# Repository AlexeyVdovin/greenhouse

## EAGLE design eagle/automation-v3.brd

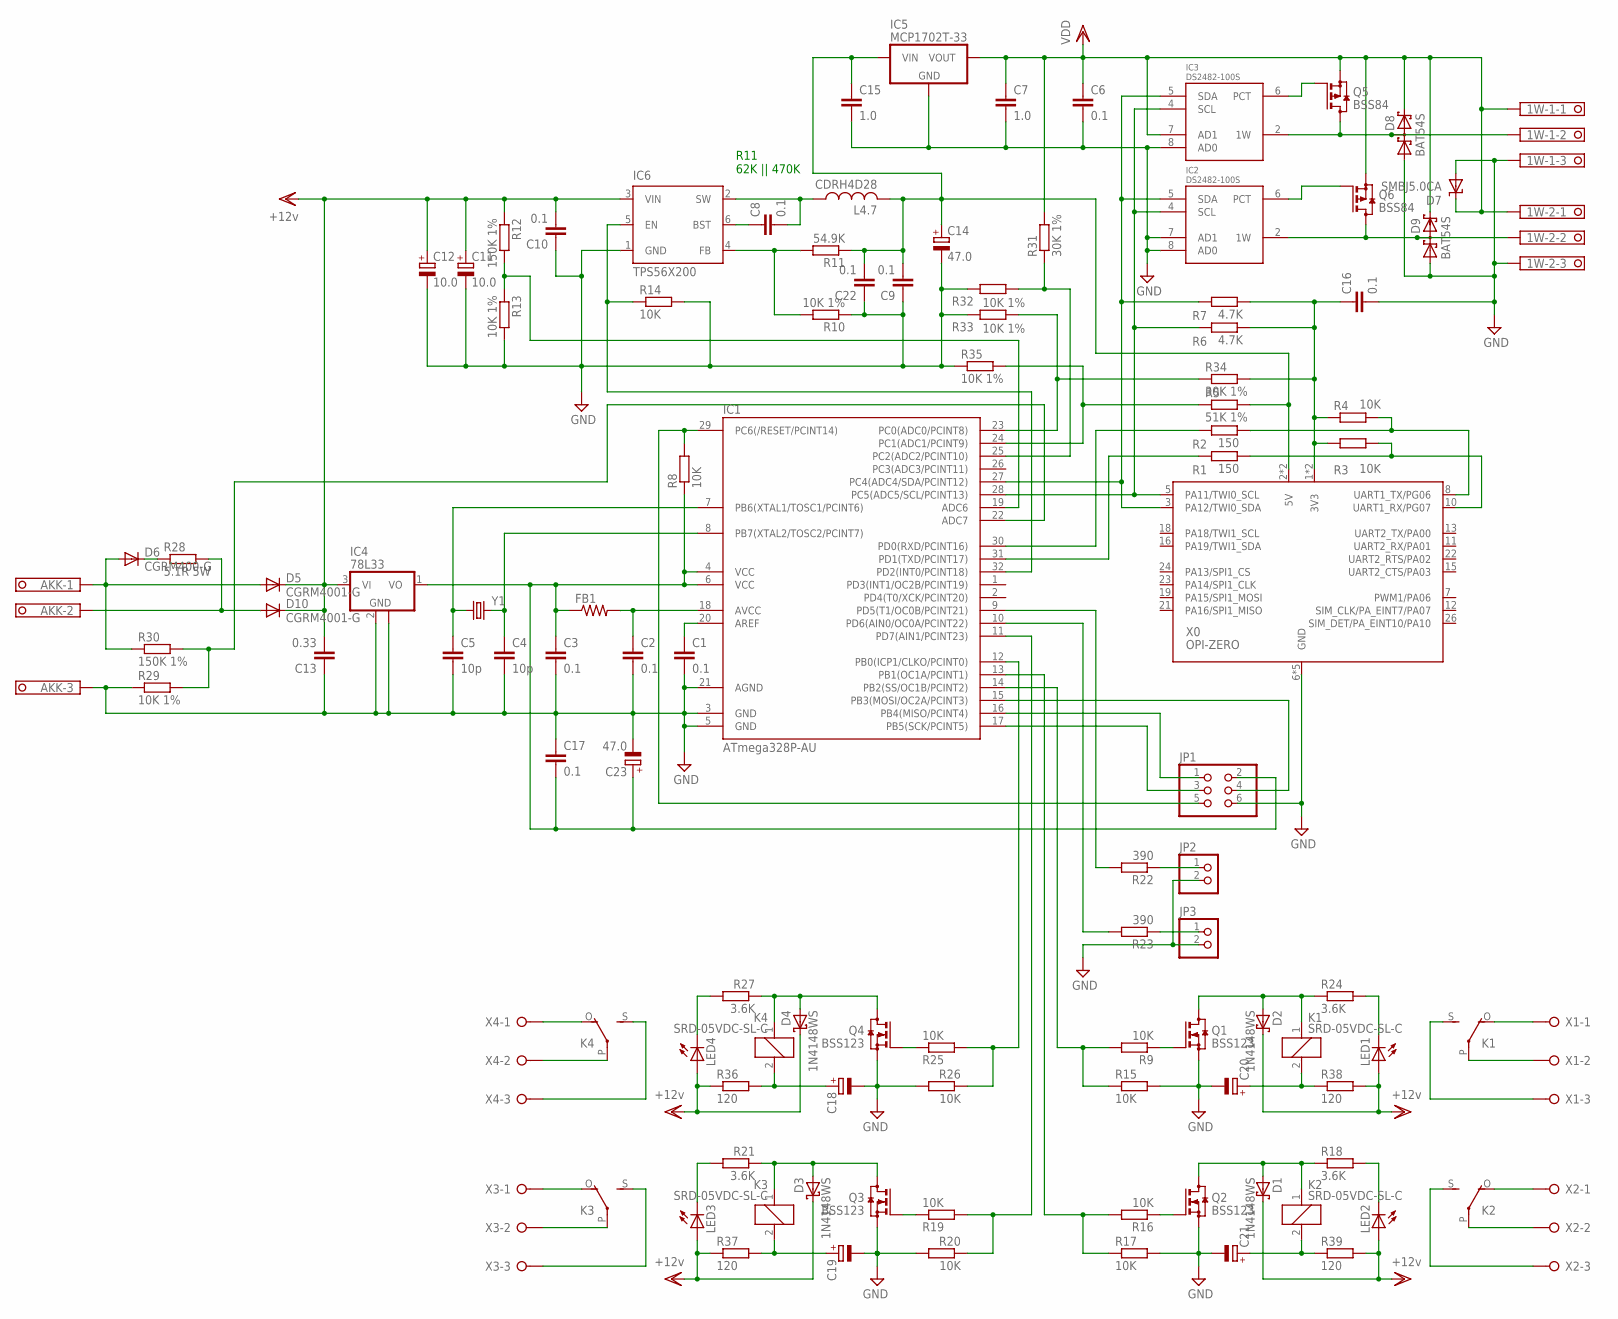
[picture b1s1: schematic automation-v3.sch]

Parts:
1W-1, 1W-2: 1751251
AKK: 1751251
C1, C2, C3, C6, C16, C17: 0.1; C0603
C4, C5: 10p; C0603
C7, C15: 1.0; C0805
C8, C9, C10, C22: 0.1; C0805
C11, C12: 10.0; C/6032-28R
C13: 0.33; C0805
C14, C23: 47.0; B/3528-21R
C18, C19, C20, C21: CPOL-EUE5-10.5; E5-10,5
D1, D2, D3, D4: 1N4148WS; SOD323_ST
D5, D10: CGRM4001-G; SOD-123_MINI-SMA
D6: CGRM400-G; SOD-123_MINI-SMA
D7: SMBJ5.0CA; SMBJ
D8, D9: BAT54S; SOT23
FB1: R-US_R0805; R0805
IC1: ATmega328P-AU; TQFP32-08
IC2, IC3: DS2482-100S; SO08
IC4: 78L33; SOT89
IC5: MCP1702T-33; SOT23-3-ROTATED
IC6: TPS56X200; TSOT23-6_DDC
JP1: PINHD-2X3; 2X03
JP2, JP3: PINHD-1X2; 1X02
K1, K2, K3, K4: SRD-05VDC-SL-C; NRP18
L4.7: CDRH4D28
LED1, LED2, LED3, LED4: LEDSML0805; SML0805
Q1, Q2, Q3, Q4: BSS123; SOT23
Q5, Q6: BSS84; SOT23
R1, R2: 150; R0603
R3, R4, R8, R9, R14, R15, R16, R17, R19, R20, R25, R26: 10K; R0603
R5: 51K 1%; R0603
R6, R7: 4.7K; R0603
R10, R13, R29, R32, R33, R35: 10K 1%; R0603
R11: 54.9K; R0603
R12, R30: 150K 1%; R0603
R18, R21, R24, R27: 3.6K; R0603
R22, R23: 390; R0603
R28: 5.1R 5W; VTA55
R31, R34: 30K 1%; R0603
R36, R37, R38, R39: 120; M1206
X0: OPI-ZERO; OPI0
X1, X2, X3, X4: W237-03P; W237-133
Y1: CRYSTALHC49US; HC49US

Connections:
12V: C10.2, C11.+, C12.+, C13.2, D1.C, D2.C, D3.C, D4.C, D5.C, D10.C, IC4.3 (VI), IC6.3 (VIN), LED1.A, LED2.A, LED3.A, LED4.A, R12.1, R36.1, R37.1, R38.2, R39.2
GND: 1W-1.3, 1W-2.3, AKK.3, C1.2, C2.2, C3.2, C4.2, C5.2, C6.2, C7.2, C9.1, C10.1, C11.-, C12.-, C13.1, C14.-, C15.2, C16.2, C17.1, C18.-, C19.-, C20.-, C21.-, C22.1, C23.-, D7.A, D8.1 (A1), D9.1 (A1), IC1.3 (GND), IC1.5 (GND), IC1.21 (AGND), IC2.3 (GND), IC2.7 (AD1), IC2.8 (AD0), IC3.3 (GND), IC3.8 (AD0), IC4.2 (GND), IC4.2@1 (GND), IC5.1 (GND), IC6.1 (GND), JP1.6, JP2.2, JP3.2, Q1.2 (S), Q2.2 (S), Q3.2 (S), Q4.2 (S), R10.1, R13.2, R14.2, R15.2, R17.2, R20.2, R26.2, R29.1, R32.2, R33.2, R35.1, X0.6 (GND), X0.9 (GND), X0.14 (GND), X0.20 (GND), X0.25 (GND)
unnamed: C8.2, IC6.2 (SW), L4.7.P$1 (1)
unnamed: C4.1, IC1.8 (PB7(XTAL2/TOSC2/PCINT7)), Y1.2
unnamed: IC1.30 (PD0(RXD/PCINT16)), R2.1
unnamed: IC1.31 (PD1(TXD/PCINT17)), R1.1
unnamed: R1.2, R3.2, X0.10 (UART1_RX/PG07)
unnamed: R2.2, R4.2, X0.8 (UART1_TX/PG06)
unnamed: C18.+, K4.2, R36.2
unnamed: C5.1, IC1.7 (PB6(XTAL1/TOSC1/PCINT6)), Y1.1
unnamed: IC1.24 (PC1(ADC1/PCINT9)), R5.1, R35.2
unnamed: AKK.1, D5.A, D6.A, R30.1
unnamed: IC1.29 (PC6(/RESET/PCINT14)), JP1.5, R8.2
unnamed: C19.+, K3.2, R37.2
unnamed: C1.1, IC1.20 (AREF)
unnamed: C2.1, FB1.2, IC1.18 (AVCC)
unnamed: C8.1, IC6.6 (BST)
unnamed: IC1.15 (PB3(MOSI/OC2A/PCINT3)), JP1.4
unnamed: IC1.17 (PB5(SCK/PCINT5)), JP1.3
unnamed: IC1.16 (PB4(MISO/PCINT4)), JP1.1
unnamed: IC3.6 (PCT), Q5.1 (G)
unnamed: IC6.4 (FB), R10.2, R11.2
unnamed: IC1.14 (PB2(SS/OC1B/PCINT2)), R9.2, R15.1
unnamed: IC1.13 (PB1(OC1A/PCINT1)), R16.2, R17.1
unnamed: IC1.19 (ADC6), R12.2, R13.1
unnamed: Q1.1 (G), R9.1
unnamed: IC1.32 (PD2(INT0/PCINT18)), IC6.5 (EN), R14.1
unnamed: K1.P, X1.2
unnamed: D6.C, R28.1
unnamed: 1W-1.2, D8.3 (C1A2), IC3.2 (1W), Q5.3 (D)
unnamed: AKK.2, D10.A, R28.2
unnamed: K1.S, X1.3
unnamed: K1.O, X1.1
unnamed: Q2.1 (G), R16.1
unnamed: D1.A, K2.1, Q2.3 (D), R18.1
unnamed: LED2.C, R18.2
unnamed: IC1.10 (PD6(AIN0/OC0A/PCINT22)), R23.2
unnamed: IC1.9 (PD5(T1/OC0B/PCINT21)), R22.2
unnamed: JP2.1, R22.1
unnamed: JP3.1, R23.1
unnamed: D2.A, K1.1, Q1.3 (D), R24.1
unnamed: K2.P, X2.2
unnamed: LED1.C, R24.2
unnamed: K2.S, X2.3
unnamed: K2.O, X2.1
unnamed: IC1.11 (PD7(AIN1/PCINT23)), R19.2, R20.1
unnamed: Q3.1 (G), R19.1
unnamed: D3.A, K3.1, Q3.3 (D), R21.1
unnamed: LED3.C, R21.2
unnamed: K3.P, X3.2
unnamed: K3.S, X3.3
unnamed: K3.O, X3.1
unnamed: IC1.12 (PB0(ICP1/CLKO/PCINT0)), R25.2, R26.1
unnamed: Q4.1 (G), R25.1
unnamed: D4.A, K4.1, Q4.3 (D), R27.1
unnamed: LED4.C, R27.2
unnamed: K4.P, X4.2
unnamed: K4.S, X4.3
unnamed: K4.O, X4.1
unnamed: 1W-2.2, D9.3 (C1A2), IC2.2 (1W), Q6.3 (D)
unnamed: IC1.22 (ADC7), R29.2, R30.2
unnamed: IC1.25 (PC2(ADC2/PCINT10)), R31.1, R32.1
unnamed: C20.+, K1.2, R38.1
unnamed: IC1.23 (PC0(ADC0/PCINT8)), R33.1, R34.1
unnamed: IC2.6 (PCT), Q6.1 (G)
unnamed: C21.+, K2.2, R39.1
SCL: IC1.28 (PC5(ADC5/SCL/PCINT13)), IC2.4 (SCL), IC3.4 (SCL), R6.1, X0.5 (PA11/TWI0_SCL)
SDA: IC1.27 (PC4(ADC4/SDA/PCINT12)), IC2.5 (SDA), IC3.5 (SDA), R7.1, X0.3 (PA12/TWI0_SDA)
VCC: C3.1, C17.2, C23.+, FB1.1, IC1.4 (VCC), IC1.6 (VCC), IC4.1 (VO), JP1.2, R8.1
VDD: 1W-1.1, 1W-2.1, C6.1, C7.1, D7.C, D8.2 (C2), D9.2 (C2), IC2.1 (VDD), IC3.1 (VDD), IC3.7 (AD1), IC5.2 (VOUT), Q5.2 (S), Q6.2 (S), R31.2
Z3V3: C16.1, R3.1, R4.1, R6.2, R7.2, R34.2, X0.1 (3V3), X0.17 (3V3)
Z5V: C9.2, C14.+, C15.1, C22.2, IC5.3 (VIN), L4.7.P$2 (2), R5.2, R11.1, X0.2 (5V), X0.4 (5V)

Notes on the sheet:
R11 62K || 470K

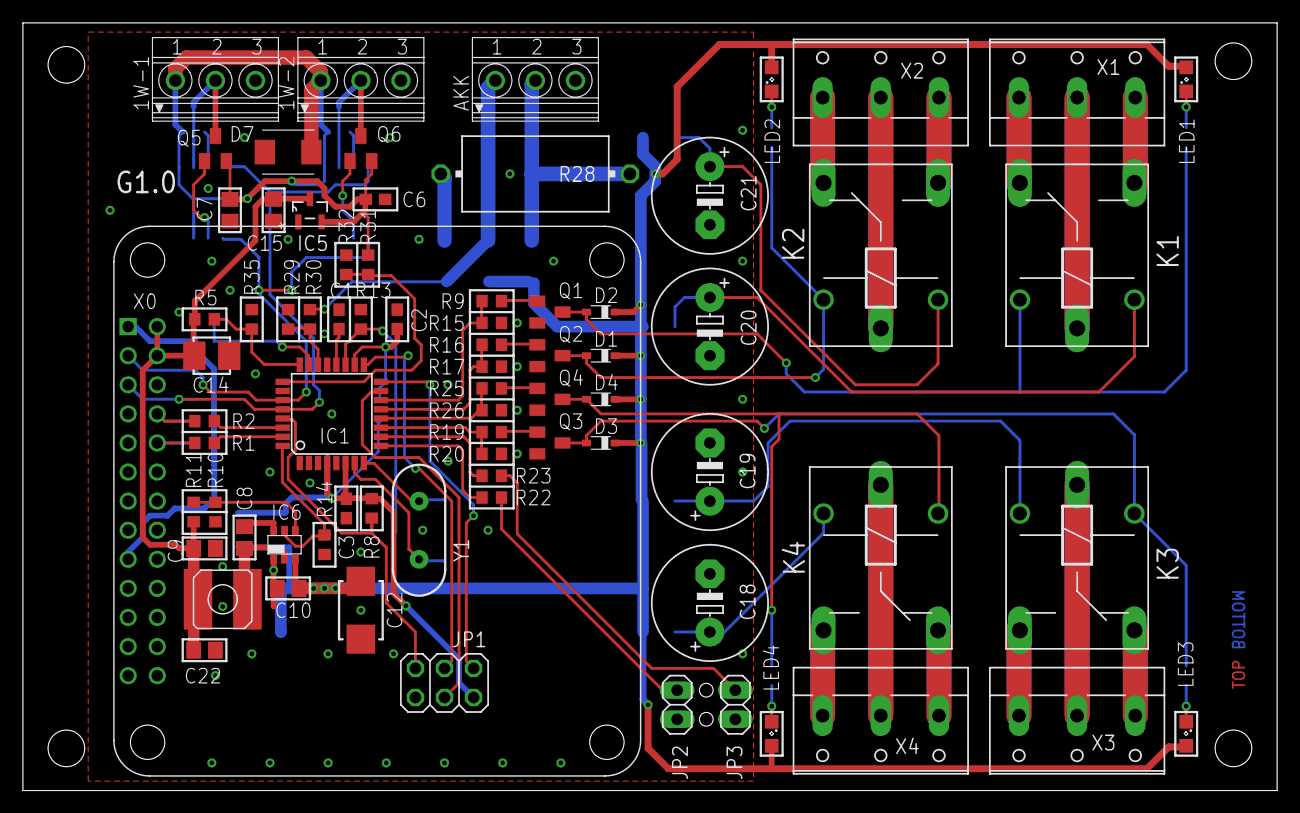
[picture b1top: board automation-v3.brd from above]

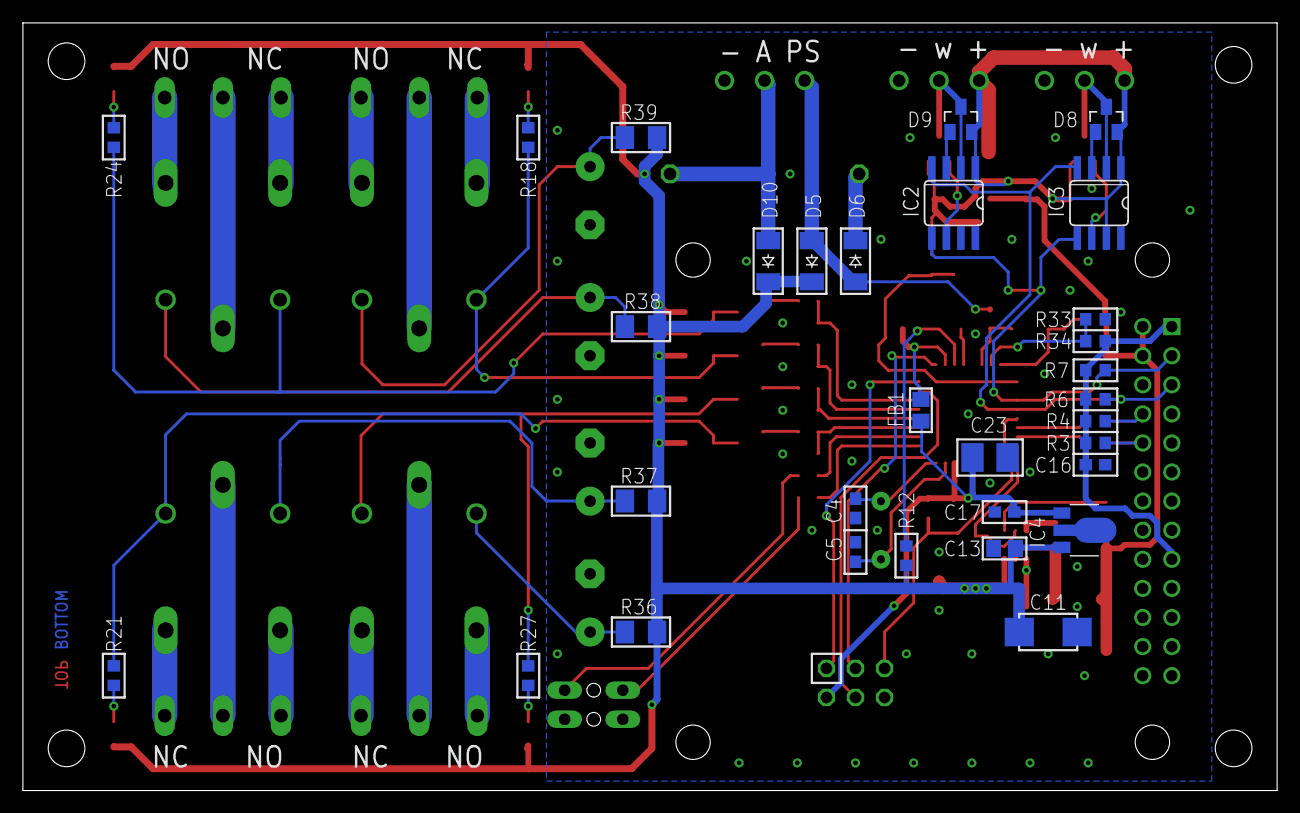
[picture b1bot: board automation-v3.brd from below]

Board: 2 copper layers, 109.5 x 67.0 mm, 106 parts (31 on the bottom side), 72 nets.

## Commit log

2018-07-10 Eagle schematic v2
2018-07-12 Initial PCB trace
2018-07-13 updated PCB trace
2018-07-13 RC version of PCB trace
2018-07-13 Replace screw clamps
2018-07-19 changed Relay footprint
2018-07-19 fix names placement
2018-07-19 strong 1w pullup added
2018-08-28 make v1.0
2018-09-01 Updated resistor values
